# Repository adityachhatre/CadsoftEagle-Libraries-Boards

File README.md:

# CadsoftEagle-Libraries-Boards

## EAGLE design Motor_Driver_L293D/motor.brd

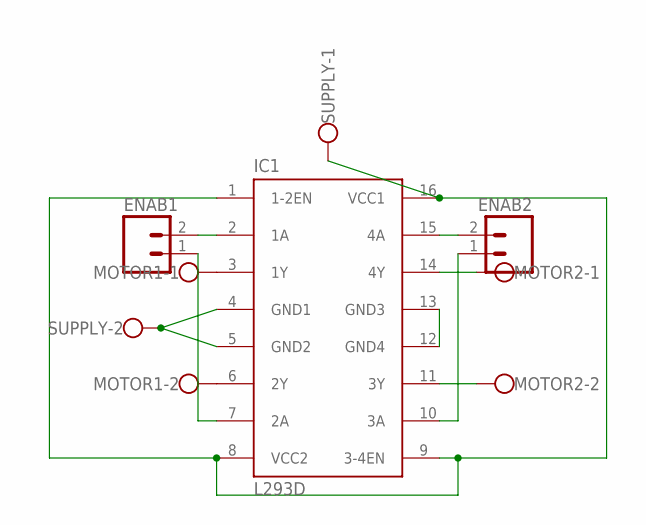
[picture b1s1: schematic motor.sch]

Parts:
ENAB1, ENAB2: M02PTH3; 1X02_LONGPADS
IC1: L293D; DIL16
MOTOR1, MOTOR2: W237-102
SUPPLY: W237-102

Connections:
GND: IC1.4 (GND1), IC1.5 (GND2), SUPPLY.2
MOTOR2: IC1.11 (3Y), MOTOR2.2
unnamed: ENAB2.2, IC1.15 (4A)
unnamed: IC1.1 (1-2EN), IC1.8 (VCC2), IC1.9 (3-4EN), IC1.16 (VCC1), SUPPLY.1
unnamed: IC1.3 (1Y), MOTOR1.1
unnamed: IC1.6 (2Y), MOTOR1.2
unnamed: IC1.12 (GND4), IC1.13 (GND3)
unnamed: ENAB1.2, IC1.2 (1A)
unnamed: ENAB2.1, IC1.10 (3A)
unnamed: ENAB1.1, IC1.7 (2A)
unnamed: IC1.14 (4Y), MOTOR2.1

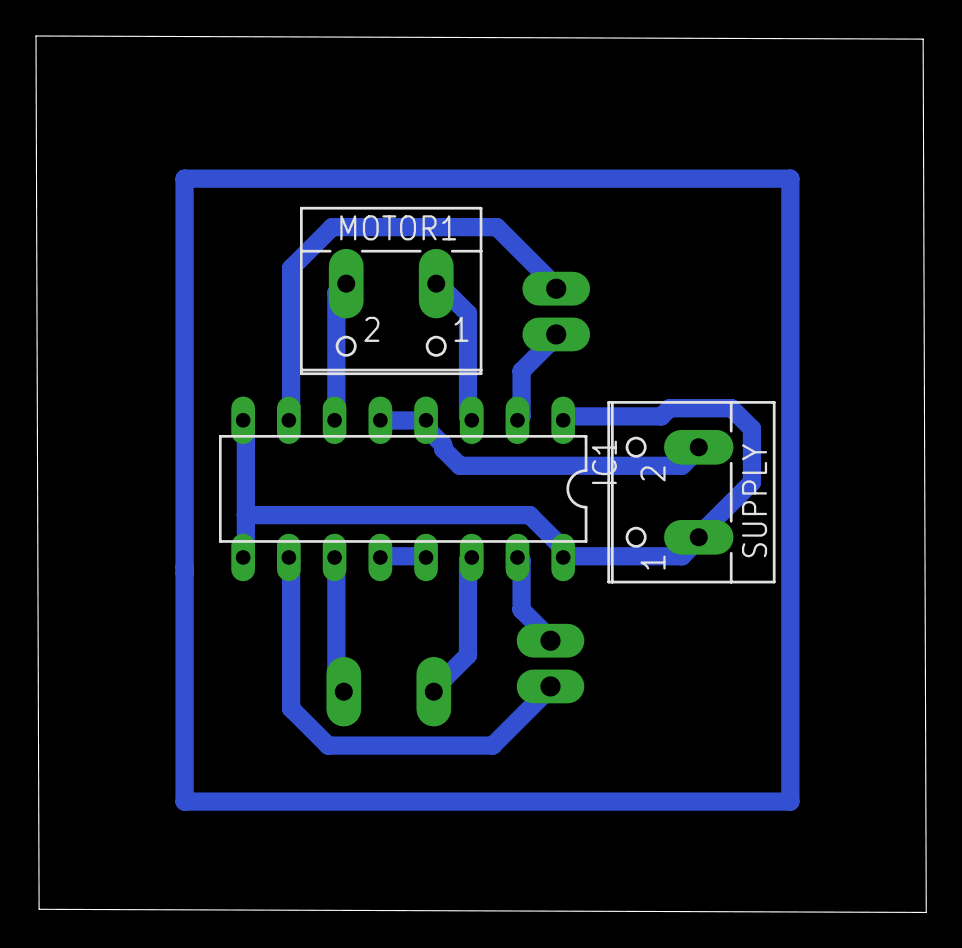
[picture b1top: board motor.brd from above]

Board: 2 copper layers, 49.5 x 48.7 mm, 6 parts (1 on the bottom side), 11 nets.

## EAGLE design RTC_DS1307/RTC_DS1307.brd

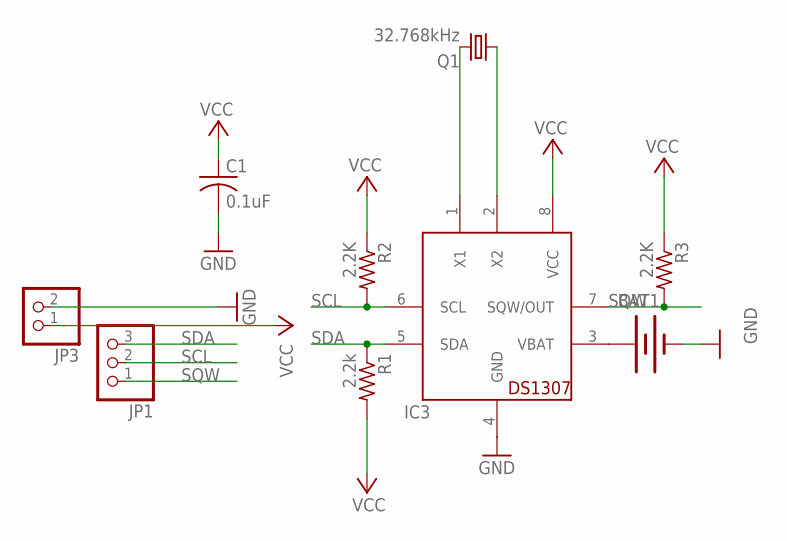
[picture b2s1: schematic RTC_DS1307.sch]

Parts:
BAT1: BATTERY20PTH; BATTCOM_20MM_PTH
C1: 0.1uF; C025-025X050
IC3: DS1307; DIL08
JP1: PINHD-1X3; 1X03
JP3: PINHD-1X2; 1X02
Q1: 32.768kHz; TC26H
R1: 2.2k; 0207/10
R2, R3: 2.2K; 0207/10

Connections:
GND: BAT1.2 (-), C1.2, IC3.4 (GND), JP3.2
unnamed: BAT1.1 (+), IC3.3 (VBAT)
unnamed: IC3.1 (X1), Q1.2
unnamed: IC3.2 (X2), Q1.1
SCL: IC3.6 (SCL), JP1.2, R2.2
SDA: IC3.5 (SDA), JP1.3, R1.1
SQW: IC3.7 (SQW/OUT), JP1.1, R3.2
VCC: C1.1, IC3.8 (VCC), JP3.1, R1.2, R2.1, R3.1

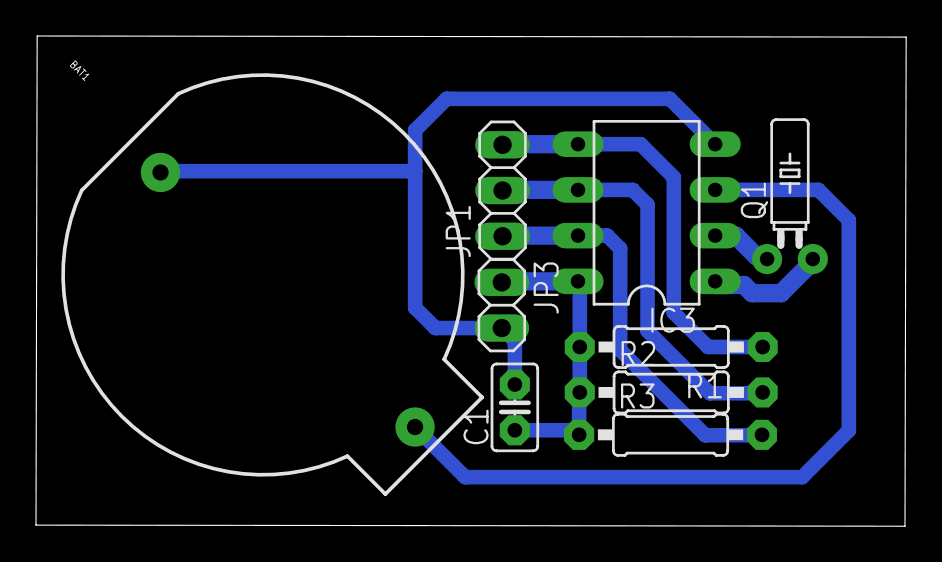
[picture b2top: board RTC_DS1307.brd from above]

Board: 2 copper layers, 48.3 x 27.2 mm, 9 parts (0 on the bottom side), 8 nets.

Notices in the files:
parts and their libraries:
SparkFun-Connectors: Licensing: CC v3.0 Share-Alike You are welcome to use this library for commercial purposes.
SparkFun-FreqCtrl: Licensing: Creative Commons ShareAlike 4.0 International - https://creativecommons.org/licenses/by-sa/4.0
